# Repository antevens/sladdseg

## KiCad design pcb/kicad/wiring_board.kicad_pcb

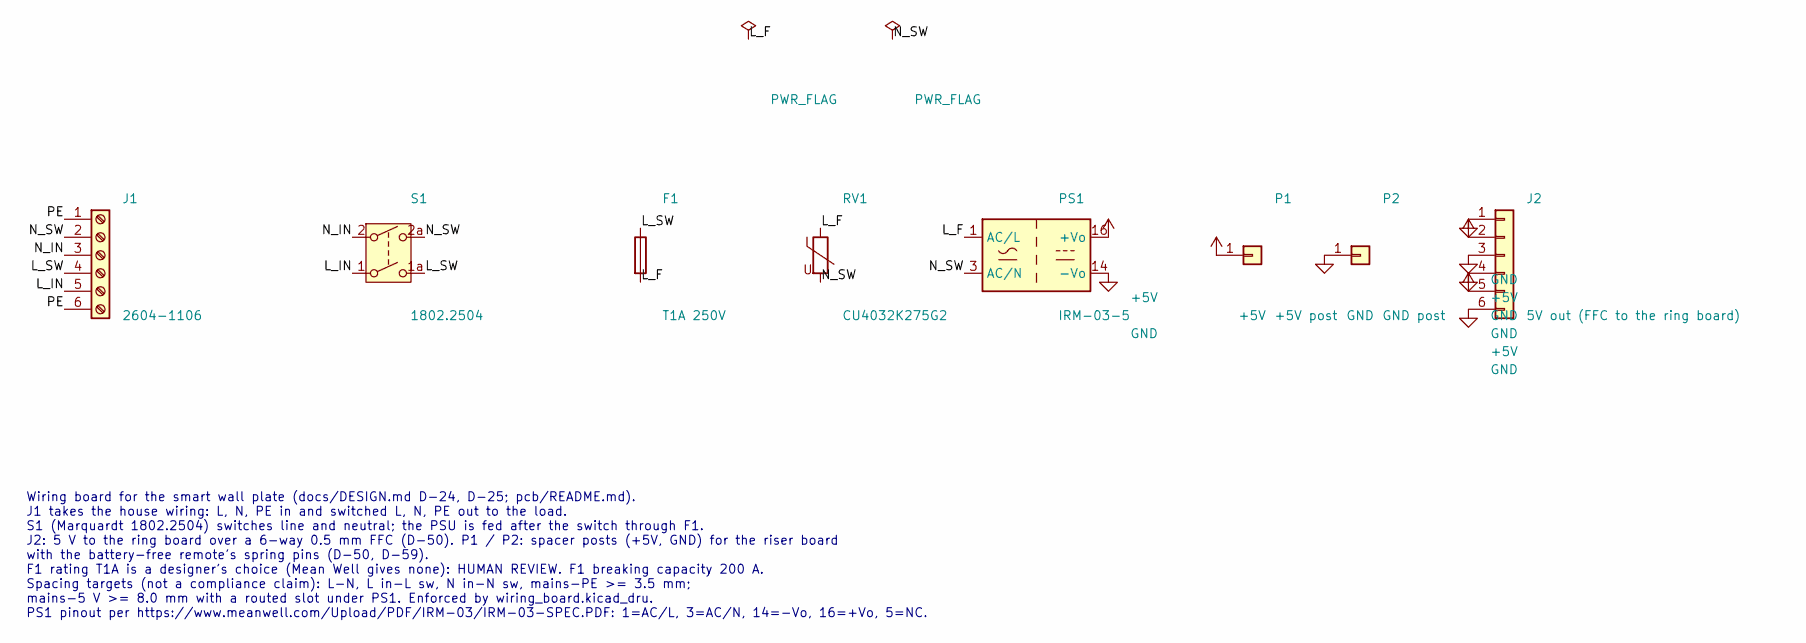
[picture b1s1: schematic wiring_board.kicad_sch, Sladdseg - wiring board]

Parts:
F1: T1A 250V; Fuse_Schurter_UMT250; MPN 3403.0166.11
J1: 2604-1106; WAGO_2604-1106_1x06_P5.00mm_Horizontal; MPN 2604-1106
J2: 5V out (FFC to the ring board); Hirose_FH12-6S-0.5SH_1x06-1MP_P0.50mm_Horizontal; MPN FH12-6S-0.5SH(55)
P1: +5V post; Wurth_WA-SMSI_M2_SMT_Spacer_L7mm; MPN 9774070243R
P2: GND post; Wurth_WA-SMSI_M2_SMT_Spacer_L7mm; MPN 9774070243R
PS1: IRM-03-5; Converter_ACDC_MeanWell_IRM-03-xx_THT; MPN IRM-03-5
RV1: CU4032K275G2; Varistor_TDK_CU4032; MPN B72660M0271K093
S1: 1802.2504; Rocker_DPST_Marquardt_1802.2504_E-Switch_RA412C1100; MPN 1802.2504

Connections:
+5V: J2.2, J2.5, P1.1, PS1.16 (+Vo)
/L_F: F1.2, PS1.1 (AC/L), RV1.1
/L_IN: J1.5, S1.1
/L_SW: F1.1, J1.4, S1.1a (2)
/N_IN: J1.3, S1.2 (3)
/N_SW: J1.2, PS1.3 (AC/N), RV1.2, S1.2a (4)
/PE: J1.1, J1.6
GND: J2.1, J2.3, J2.4, J2.6, P2.1, PS1.14 (-Vo)

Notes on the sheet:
Wiring board for the smart wall plate (docs/DESIGN.md D-24, D-25; pcb/README.md). J1 takes the house wiring: L, N, PE in and switched L, N, PE out to the load. S1 (Marquardt 1802.2504) switches line and neutral; the PSU is fed after the switch through F1. J2: 5 V to the ring board over a 6-way 0.5 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

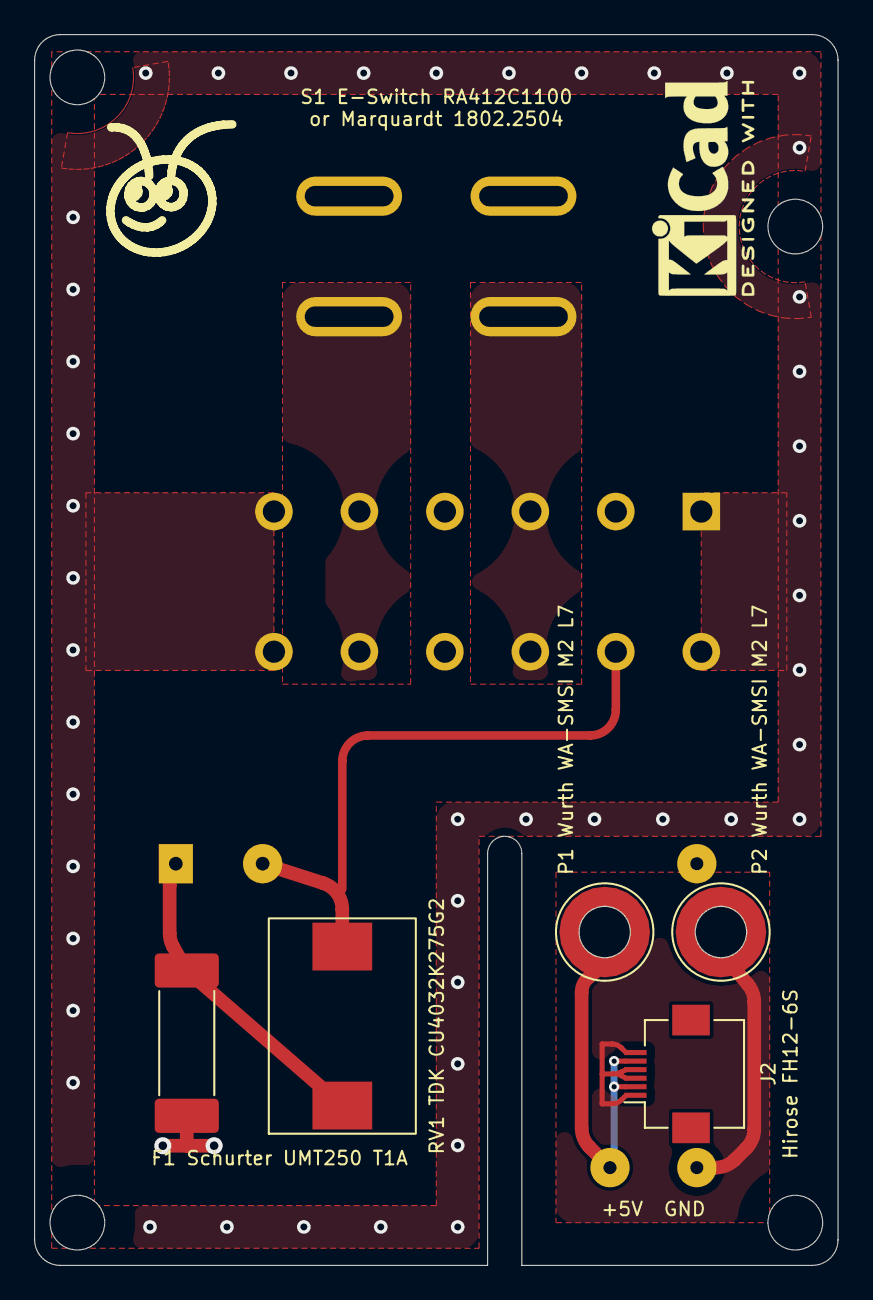
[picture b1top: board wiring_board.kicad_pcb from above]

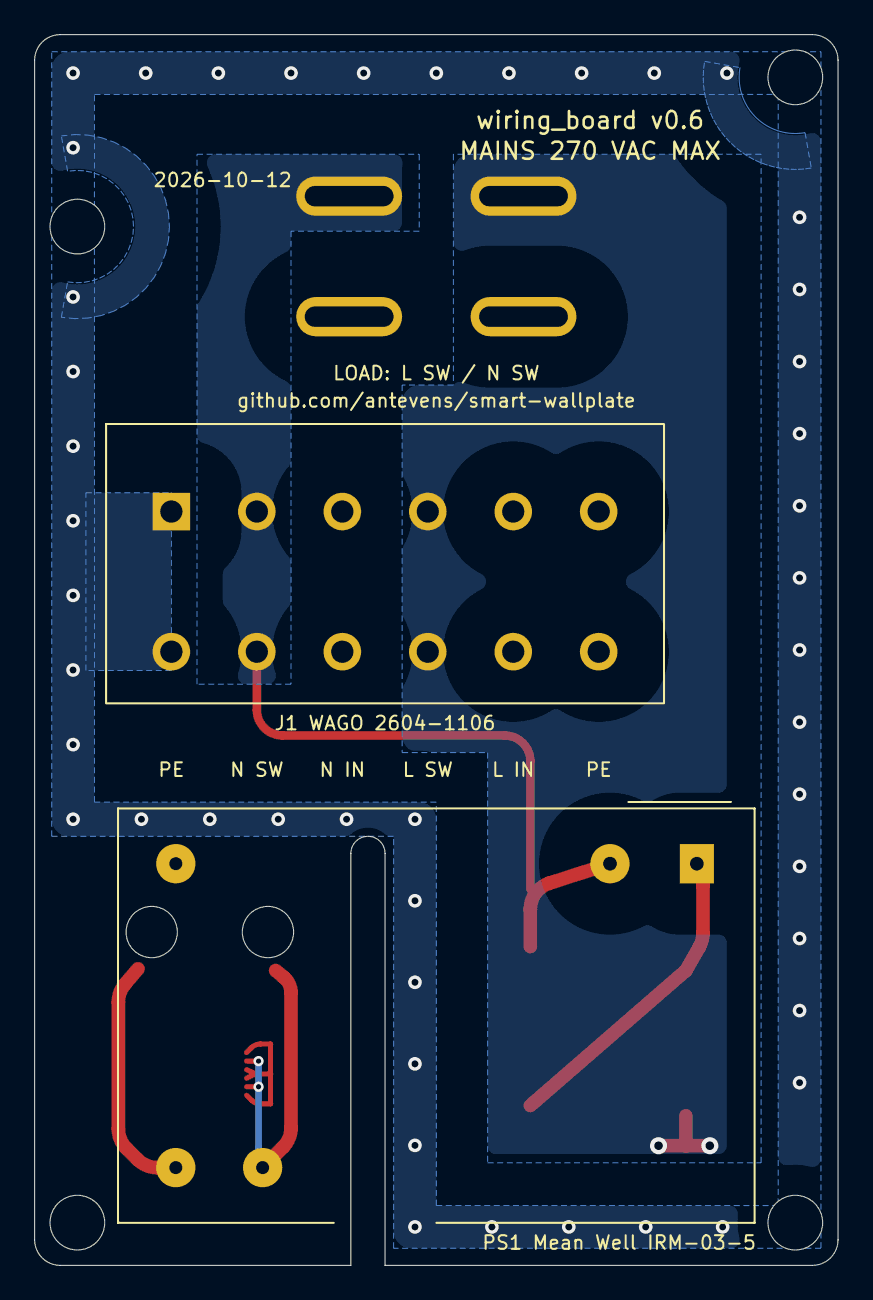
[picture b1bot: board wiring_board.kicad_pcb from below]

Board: 2 copper layers, 47.0 x 72.0 mm, 14 parts (2 on the bottom side), 8 nets.

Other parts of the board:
LOGO1: Ant_Logo_8mm_SilkScreen
LOGO2: KiCad-Logo2_5mm_SilkScreen
MH1, MH2, MH3, MH4: MountingHole_3.2mm_M3_NPTH

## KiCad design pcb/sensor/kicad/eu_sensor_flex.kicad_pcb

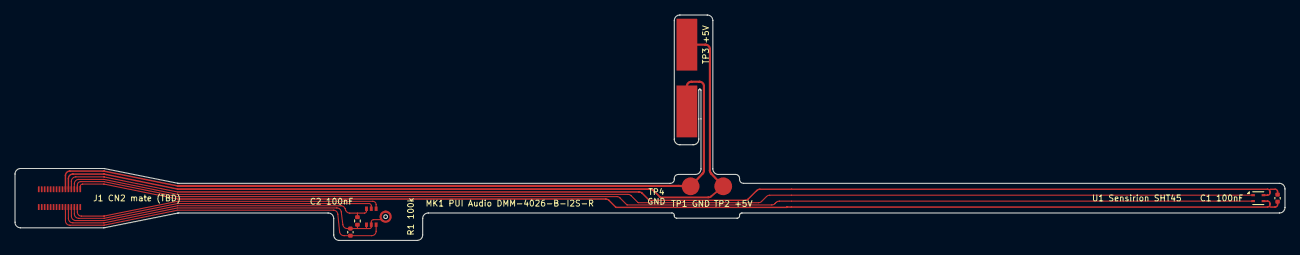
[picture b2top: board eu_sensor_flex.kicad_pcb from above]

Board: 2 copper layers, 171.3 x 30.4 mm, 10 parts (0 on the bottom side), 11 nets.

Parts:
C1, C2: 100nF; C_0402_1005Metric
J1: CN2 mate (TBD); B2B_0.4mm_2x15_PLACEHOLDER
MK1: DMM-4026-B-I2S-R; PUI_DMM-4026-B-I2S_4x3mm
R1: 100k; R_0402_1005Metric
TP1: GND pin pad; Contact_Pad_D2.4mm
TP2: +5V pin pad; Contact_Pad_D2.4mm
TP3: +5V floor pad; Contact_Pad_2.9x7mm
TP4: GND floor pad; Contact_Pad_2.9x7mm
U1: SHT45; Sensirion_DFN-4_1.5x1.5mm_P0.8mm_SHT4x_NoCentralPad

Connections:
+3V3: C1.1, J1.29, U1.3
+5V: J1.21, TP2.1, TP3.1
/GND_SHT: C1.2, J1.23, U1.4
/I2S_SCK: J1.26, MK1.6
/I2S_SD: J1.24, MK1.7, R1.2
/I2S_WS: J1.28, MK1.5
/MIC_3V3: C2.1, J1.20, MK1.3
/MIC_GND: C2.2, J1.22, MK1.1, MK1.2, MK1.4, R1.1
/SCL: J1.27, U1.2
/SDA: J1.25, U1.1
GND: J1.19, TP1.1, TP4.1

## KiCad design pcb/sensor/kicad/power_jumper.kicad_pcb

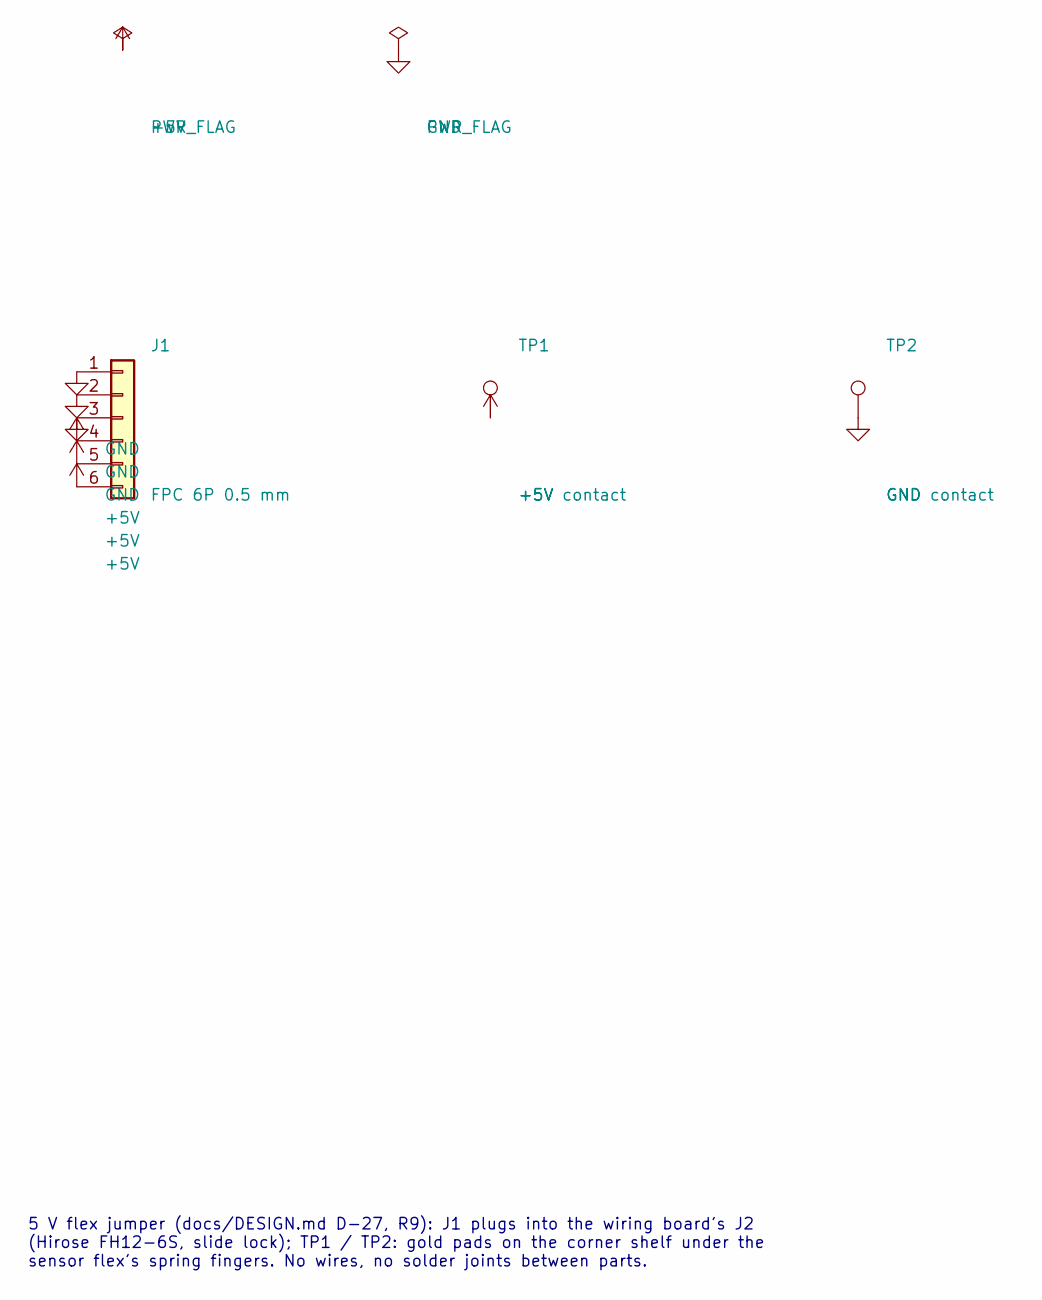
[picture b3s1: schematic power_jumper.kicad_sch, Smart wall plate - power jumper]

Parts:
J1: FPC 6P 0.5 mm; FPC_6P_P0.50mm_Contacts
TP1: +5V contact; Contact_Pad_2.2x4.5mm
TP2: GND contact; Contact_Pad_2.2x4.5mm

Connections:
+5V: J1.4, J1.5, J1.6, TP1.1
GND: J1.1, J1.2, J1.3, TP2.1

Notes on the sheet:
5 V flex jumper (docs/DESIGN.md D-27, R9): J1 plugs into the wiring board's J2 (Hirose FH12-6S, slide lock); TP1 / TP2: gold pads on the corner shelf under the sensor flex's spring fingers. No wires, no solder joints between parts.

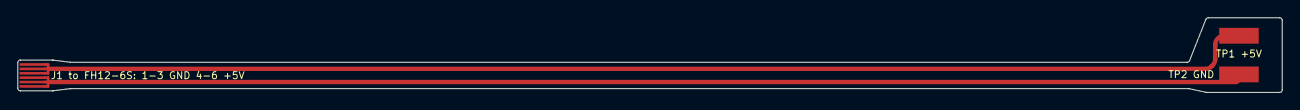
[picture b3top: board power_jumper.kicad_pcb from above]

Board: 2 copper layers, 144.0 x 8.5 mm, 3 parts (0 on the bottom side), 2 nets.

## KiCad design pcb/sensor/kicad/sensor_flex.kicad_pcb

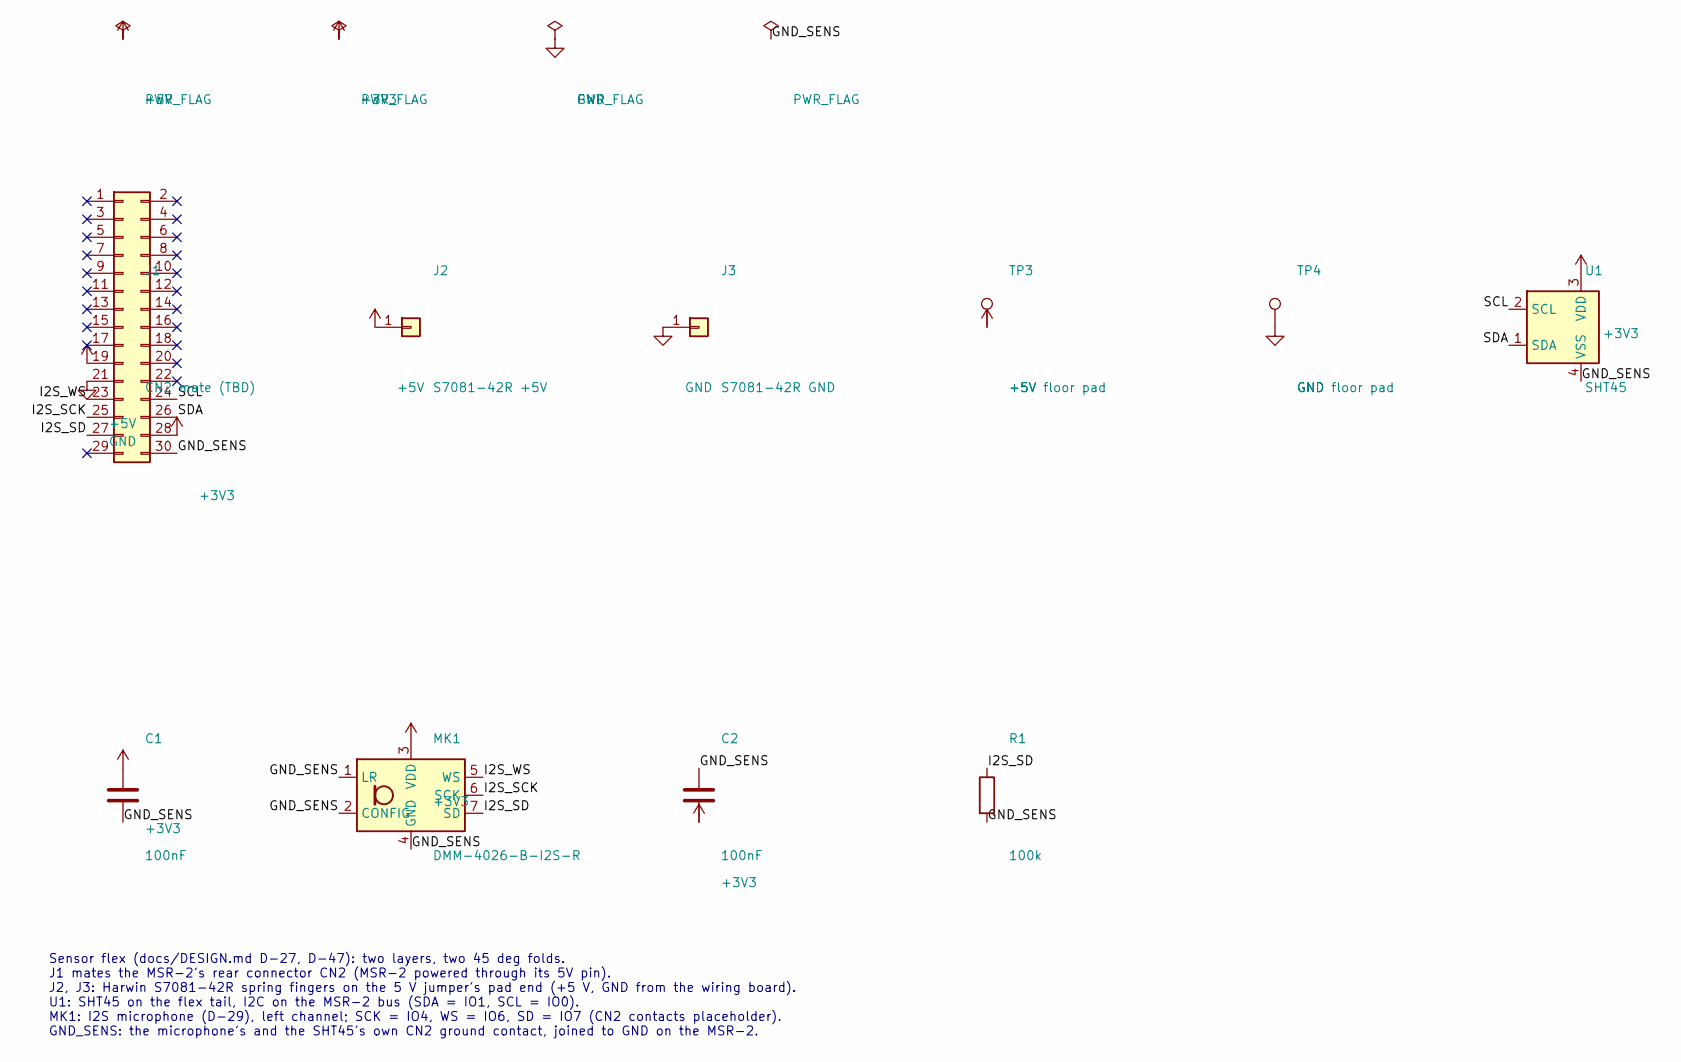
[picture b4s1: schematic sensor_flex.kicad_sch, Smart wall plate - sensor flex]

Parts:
C1, C2: 100nF; C_0402_1005Metric; MPN 0402 X7R 100 nF 16 V
J1: CN2 mate (TBD); B2B_0.4mm_2x15_PLACEHOLDER; MPN TBD
J2: S7081-42R +5V; Harwin_S7081-42R; MPN S7081-42R
J3: S7081-42R GND; Harwin_S7081-42R; MPN S7081-42R
MK1: DMM-4026-B-I2S-R; PUI_DMM-4026-B-I2S_4x3mm; MPN DMM-4026-B-I2S-R
R1: 100k; R_0402_1005Metric; MPN 0402 1% 100 kOhm
TP3: +5V floor pad; Contact_Pad_7x4mm
TP4: GND floor pad; Contact_Pad_7x4mm
U1: SHT45; Sensirion_DFN-4_1.5x1.5mm_P0.8mm_SHT4x_NoCentralPad; MPN SHT45-AD1B-R2

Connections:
+3V3: C1.1, C2.2, J1.28, MK1.3 (VDD), U1.3 (VDD)
+5V: J1.19, J2.1, TP3.1
/GND_SENS: C1.2, C2.1, J1.30, MK1.1 (LR), MK1.2 (CONFIG), MK1.4 (GND), R1.2, U1.4 (VSS)
/I2S_SCK: J1.25, MK1.6 (SCK)
/I2S_SD: J1.27, MK1.7 (SD), R1.1
/I2S_WS: J1.23, MK1.5 (WS)
/SCL: J1.24, U1.2 (SCL)
/SDA: J1.26, U1.1 (SDA)
GND: J1.21, J3.1, TP4.1

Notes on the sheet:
Sensor flex (docs/DESIGN.md D-27, D-47): two layers, two 45 deg folds. J1 mates the MSR-2's rear connector CN2 (MSR-2 powered through its 5V pin). J2, J3: Harwin S7081-42R spring fingers on the 5 V jumper's pad end (+5 V, GND from the wiring board). U1: SHT45 on the flex tail, I2C on the MSR-2 bus 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

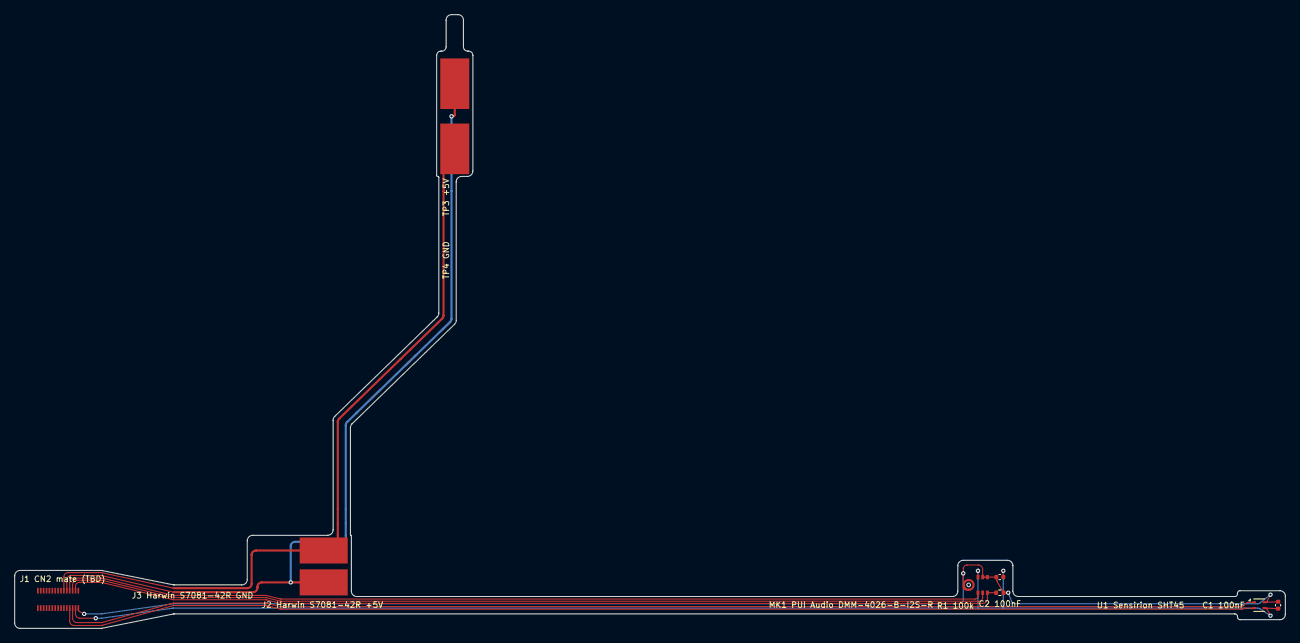
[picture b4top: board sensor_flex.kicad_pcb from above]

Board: 2 copper layers, 175.5 x 84.7 mm, 10 parts (0 on the bottom side), 9 nets.
